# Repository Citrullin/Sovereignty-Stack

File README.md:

# Sovereignty Stack: Federated, Post-ICANN Sovereignty

### A Verifiable, Full-Stack Architecture Bridging Physical Hardware & Cryptographic Manifolds

---

## 1. The Vision

The classical centralized internet and monolithic public blockchain paradigms have reached their limits. Monolithic architectures, burdened by global consensus constraints, speculative volatility, and governance cartels, fail to scale for localized, real-world coordination.

The **Sovereign Stack** bypasses these legacy constraints. Instead of anchoring to central public chains, it coordinates independent, localized **Sector Manifolds** in an autonomous **Sovereign Mesh**. These manifolds peer directly with one another, routing assets and state changes peer-to-peer using **Althea BGP routing** and **cross-manifold Lock mechanisms**, verified via hardware attestation and decentralized proofs.

```mermaid
graph TD
    subgraph Client Layer [Edge Client & Authentication]
        User["NFC Disc / Passkey (3FSA)"] -->|Offline NFC Tap| Node["Local Manifold Node"]
        User -->|SIWE-OIDC Bridge| Koral["Koral Hub: Nextcloud, Gitea, ERPNext"]
    end

    subgraph Execution Layer [Sector Manifolds]
        Node -->|FCFS Tx Pool| Reth["sovereign-reth Stateless Engine"]
        Reth -->|Stateless WitnessDB| WASM["PGlite WASM Edge Sync"]
        Reth -->|6LoWPAN / UDP Mesh| Mesh["Embedded Mesh Network (Avalanche Snow)"]
    end

    subgraph Coordination Layer [Sovereign Mesh & Auditing]
        Reth -->|CMIP / BGP Route| BGP["Althea Pay-per-Forward BGP Routing"]
        BGP -->|Cross-Manifold Locks| Settlement["P2P Settlement & Namespace Enforcement"]
        Audit["DAO Verifiable Auditing"] -->|DAS & Witness Proofs| IPFS["IPFS Storage"]
    end

    style Node fill:#1e222a,stroke:#528bff,stroke-width:1.5px,color:#abb2bf
    style Reth fill:#1e222a,stroke:#528bff,stroke-width:1.5px,color:#abb2bf
    style BGP fill:#1e222a,stroke:#98c379,stroke-width:1.5px,color:#abb2bf
    style Koral fill:#1e222a,stroke:#c678dd,stroke-width:1px,color:#abb2bf
```

This is a pragmatic, local-first approach to decentralization: bringing real-world systems, self-hosted services, and physical industrial hardware together and enforcing coordination via verifiable cryptography.

---

## 2. Key Architecture Components

- **Physicalization of Trust (L0 Hardware):** Trust is anchored directly in physical hardware. `sovereign-reth` runs on bare-metal physical nodes and smart [bit.block microbricks](hardware/bit.block/), using physical [NFC Social Badges](hardware/tiny-pay/) for 3-Factor Sovereign Auth and Crypto-Native Cash (using post-quantum W-OTS+).
- **Post-ICANN BGP Routing & Namespace Enforcement:** Manifolds function as Autonomous Systems (AS), completely replacing legacy IP/DNS. Cross-manifold transactions are routed like IP packets using Althea pay-per-forward economics and dynamic BGP negotiations with complete namespace enforcement.
- **Stateless Execution (`sovereign-reth` & Blind Courier):** Nodes operate statelessly on physical edge hardware, implementing **Blind Courier** for private, stateless witness routing. Embedded WASM CRDT databases (PGlite) handle zero-latency edge synchronization.
- **Universal `did:peer:4` Identity:** Decentralized identities replace IPs and Web2 logins. A single 256-bit entropy seed derives keys for EVM execution (secp256k1), WireGuard peering (Ed25519), and Sync Committees (BLS12-381) via BIP-32.
- **Decentralized Service Level Agreements (DSLA):** Subjective legal contracts are replaced by deterministic hardware **Heartbeat Oracles** and **Actuator Kill-Switches** enforcing pre-emptive compliance.
- **Automated Epistemology Engine:** A machine-verifiable pipeline that binds sociological intent ([Gherkin scenarios](docs/architecture/testing/features/)) to formal mathematical specifications (TLA+) and cryptographically signed execution traces ([OCI/TPM attestations](docs/architecture/verification/51_confidential_deployment_oci_surgery.md)). This forms the absolute truth boundary of the manifold by modeling a **Quantum Superposition** of all possible agent outcomes.

---

## 3. How to Read This Repository

The Sovereign Stack is a theory-driven architecture. The repository is structured to guide you from foundational physics to technical implementation:

1. 📚 **[Quantum Social Physics (QSP) Paper](QUANTUM_SOCIAL_PHYSICS.md):** Start here. This academic paper defines the formal mathematics behind the stack (Velocity Economics, Topological Pathologies, and Resonant Coherence).
2. 📖 **[The Whitebook](whitebook/):** A comprehensive 15-chapter technical specification detailing how the QSP theory is implemented across Identity, Execution, Routing, and Physical Infrastructure.
3. 🧠 **[Concepts Archive](concepts/):** A rich directory of 36 deep-dive philosophical and technical essays expanding on individual mechanics.
4. 💻 **[`sovereign-reth` Execution Engine](crates/):** The Rust implementation of the Sovereign Stack, featuring custom FCFS transaction pools, stateless execution, and cross-manifold BGP intent routing.

---

## 4. Trust & Security Taxonomy

We approach sovereignty not as a collection of apps, but as a formally verifiable ecosystem defined by a strict **Trust Taxonomy**:
- **L0 (Hardware):** Secure Elements and hardware entropy.
- **L1 (Kernel/OS):** Strict deterministic process isolation.
- **L2 (Network):** Metadata obfuscation and privacy routing.
- **L3 (Identity):** Cryptographically defined DIDs and Verifiable Credentials.
- **L4 (User Agency):** UI/UX designed to prevent dark patterns and enforce informed consent.

The stack solves the "Sovereignty Gap" by replacing the "Trust but Verify" paradigm with a **"Verify, then Trust"** architecture. Through Decentralized Verification, Zero-Trust Orchestration, and transparent threat modeling, the stack guarantees that users own not just their data, but the orchestration logic itself.

### Strategic Roadmap: Eliminating Operator Trust

| Component | Legacy Model | Sovereign Recommendation | Why? |
| :--- | :--- | :--- | :--- |
| **Logic** | Helm / Jinja | OCI Layer Patches (`umoci`) | Eliminates template injection/leaks. |
| **Integrity** | Ansible Scripts | `in-toto` Attestations | Cryptographic proof of physical & digital "Why/How". |
| **Isolation** | Standard Podman | Confidential Containers (CoCo) | Host cannot read container memory. |
| **Trust Root** | Admin Password | Keylime + TPM 2.0 | Hardware-level detection of physical tampering. |
| **Build Env** | Shared VM/Runner | TEE (Intel TDX / AMD SEV) | Build process is a "Black Box" even to root. |

For the formal threat model, see [`docs/architecture/THREAT_MODEL.md`](docs/architecture/THREAT_MODEL.md).
For the tunneling protocol and intent-based routing, see the [Unified Manifold Interface (UMI)](docs/architecture/UNIFIED_MANIFOLD_INTERFACE.md).

---

## 5. Repository Directory Index

The repository contains both hardware specifications and software execution engines:

| Directory | Sub-components & Function | Key Concept Chapters |
|---|---|---|
| [`whitebook/`](whitebook/) | Comprehensive 15-chapter technical specifications. | §01–§15 |
| [`concepts/`](concepts/) | Concept manifesto, $TINY tokenomics, and proof-of-work anchors. | §00–§54 |
| [`hardware/bit.block/`](hardware/bit.block/) | Smart microbrick PCB (KiCAD), 3D prints, and WebGL emulator. | §12, §13, §11 |
| [`hardware/gachapon/`](hardware/gachapon/) | Gachapon machine design — Physicalized Based Rollup Node. | §03, §15, §22 |
| [`hardware/tiny-pay/`](hardware/tiny-pay/) | NFC Tiny Disc (Social Badge + Wahfare branded disc). | §22, §18, §43 |
| [`hardware/tinyblock/`](hardware/tinyblock/) | LDraw set designs (Astronaut, Lighthouse). | §44 |
| [`software/bit.block/`](software/bit.block/) | Arduino WoT firmware — W3C Thing Description PoC. | §12, §16, §11 |
| [`software/tinyblock/`](software/tinyblock/) | LDraw parts submodule + AI training benchmark images. | §44 |
| [`software/web-of-things/`](software/web-of-things/) | RIOT-OS WoT + Arduino WebThings submodules. | §12, §13 |
| [`software/koral/`](software/koral/) | Sovereign Hub — k8s, Nextcloud, ERPNext, OIDC, Istio. | §04, §16, §18, §46 |
| [`software/chain/`](software/chain/) | Smart contract specs: $TINY, ERC-3475, deIBAN. | §39–§43, §46 |

---

## 6. Quick Start

Clone the repository and initialize all hardware/software submodules:

```bash
# Clone with submodules
git clone --recurse-submodules https://github.com/citrullin/sovereign_stack_vision.git

# Or if already cloned, initialize submodules:
git submodule update --init
```

### Submodules Included:
- `software/tinyblock/microblock_ldraw`: LDraw parts library for physical microblocks.
- `software/web-of-things/RIOT-OS`: W3C WoT CoAP module for IoT RIOT-OS.
- `software/web-of-things/arduino`: WebThings fork (WoT TD 1.0) for Arduino/ESP32.

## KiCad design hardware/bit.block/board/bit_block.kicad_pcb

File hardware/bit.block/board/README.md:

# PCB Files for the Astronaut on Moon Base Set

The offline local-only voice recognition tinyblock set. Full KiCAD files in this directory.

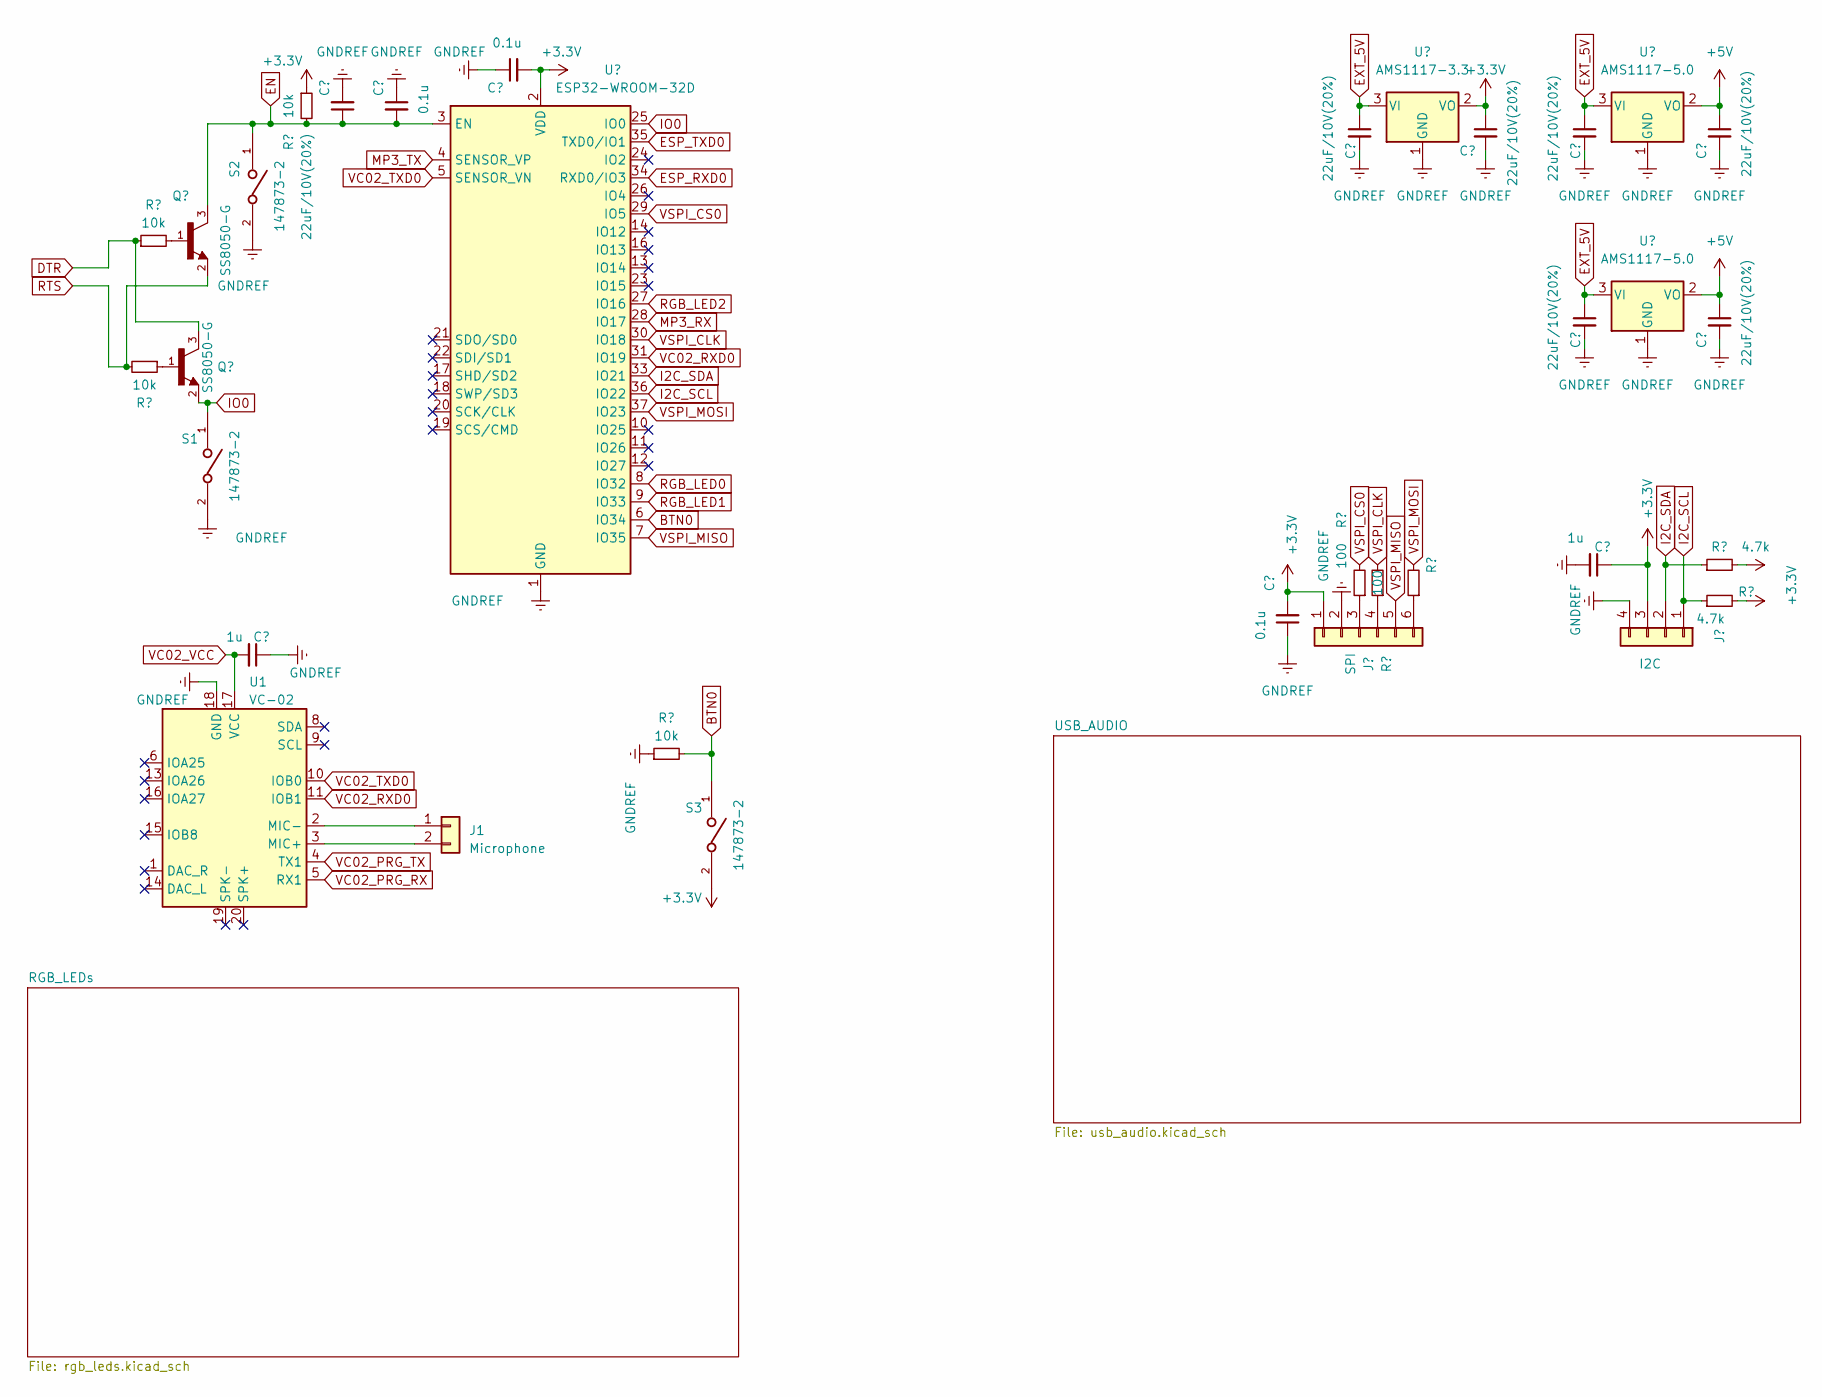
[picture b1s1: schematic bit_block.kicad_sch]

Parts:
C1, C10: 1u; C_0402_1005Metric
C2, C6, C7, C8, C9, C11, C12: 22uF/10V(20%); CP_EIA-3216-18_Kemet-A
C3, C4, C5: 0.1u; C_0402_1005Metric
J1: Microphone; PinHeader_1x02_P2.00mm_Vertical
J2: SPI; JST_SH_SM06B-SRSS-TB_1x06-1MP_P1.00mm_Horizontal
J3: I2C; JST_SH_SM04B-SRSS-TB_1x04-1MP_P1.00mm_Horizontal
Q1, Q2: SS8050-G; TRANS_SS8050-G; PARTREV A
R1, R2, R3, R4: 10k; R_0402_1005Metric
R5, R6, R7: 100; R_0402_1005Metric
R8, R9: 4.7k; R_0402_1005Metric
S1, S2, S3: 147873-2; SW_147873-2; PARTREV K3
U1: VC-02; Ai-Thinker-VC02
U2: ESP32-WROOM-32D; ESP32-WROOM-32
U3: AMS1117-3.3; SOT-223-3_TabPin2
U4, U5: AMS1117-5.0; SOT-223-3_TabPin2

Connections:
+3.3V: C4.2, C5.2, C7.1, C10.1, J2.1, J3.3, R3.1, R8.2, R9.2, S3.2, U2.2 (VDD), U3.2 (VO); also elsewhere on the board
+5V: C11.1, C12.1, U4.2 (VO), U5.2 (VO); also elsewhere on the board
BTN0: R4.2, S3.1, U2.6 (IO34)
DTR: Q1.3, R2.1; also elsewhere on the board
EN: C2.1, C3.2, Q2.3, R3.2, S2.1, U2.3 (EN)
ESP_RXD0: U2.34 (RXD0/IO3); also elsewhere on the board
ESP_TXD0: U2.35 (TXD0/IO1); also elsewhere on the board
EXT_5V: C6.1, C8.1, C9.1, U3.3 (VI), U4.3 (VI), U5.3 (VI); also elsewhere on the board
GNDREF: C1.1, C2.2, C3.1, C4.1, C5.1, C6.2, C7.2, C8.2, C9.2, C10.2, C11.2, C12.2, J2.2, J3.4, R4.1, S1.2, S2.2, U1.18 (GND), U2.1 (GND), U2.15 (GND), U2.38 (GND), U2.39 (GND), U3.1 (GND), U4.1 (GND), U5.1 (GND); also elsewhere on the board
I2C_SCL: J3.1, R9.1, U2.36 (IO22)
I2C_SDA: J3.2, R8.1, U2.33 (IO21)
IO0: Q1.2, S1.1, U2.25 (IO0)
MP3_RX: U2.28 (IO17); also elsewhere on the board
MP3_TX: U2.4 (SENSOR_VP); also elsewhere on the board
unnamed: J1.1, U1.2 (MIC-)
unnamed: J1.2, U1.3 (MIC+)
unnamed: J2.3, R5.1
unnamed: J2.4, R6.1
unnamed: J2.6, R7.1
unnamed: Q1.1, R1.1
unnamed: Q2.1, R2.2
RGB_LED0: U2.8 (IO32); also elsewhere on the board
RGB_LED1: U2.9 (IO33); also elsewhere on the board
RGB_LED2: U2.27 (IO16); also elsewhere on the board
RTS: Q2.2, R1.2; also elsewhere on the board
VC02_PRG_RX: U1.5 (RX1); also elsewhere on the board
VC02_PRG_TX: U1.4 (TX1); also elsewhere on the board
VC02_RXD0: U1.11 (IOB1), U2.31 (IO19)
VC02_TXD0: U1.10 (IOB0), U2.5 (SENSOR_VN)
VC02_VCC: C1.2, U1.17 (VCC); also elsewhere on the board
VSPI_CLK: R6.2, U2.30 (IO18)
VSPI_CS0: R5.2, U2.29 (IO5)
VSPI_MISO: J2.5, U2.7 (IO35)
VSPI_MOSI: R7.2, U2.37 (IO23)

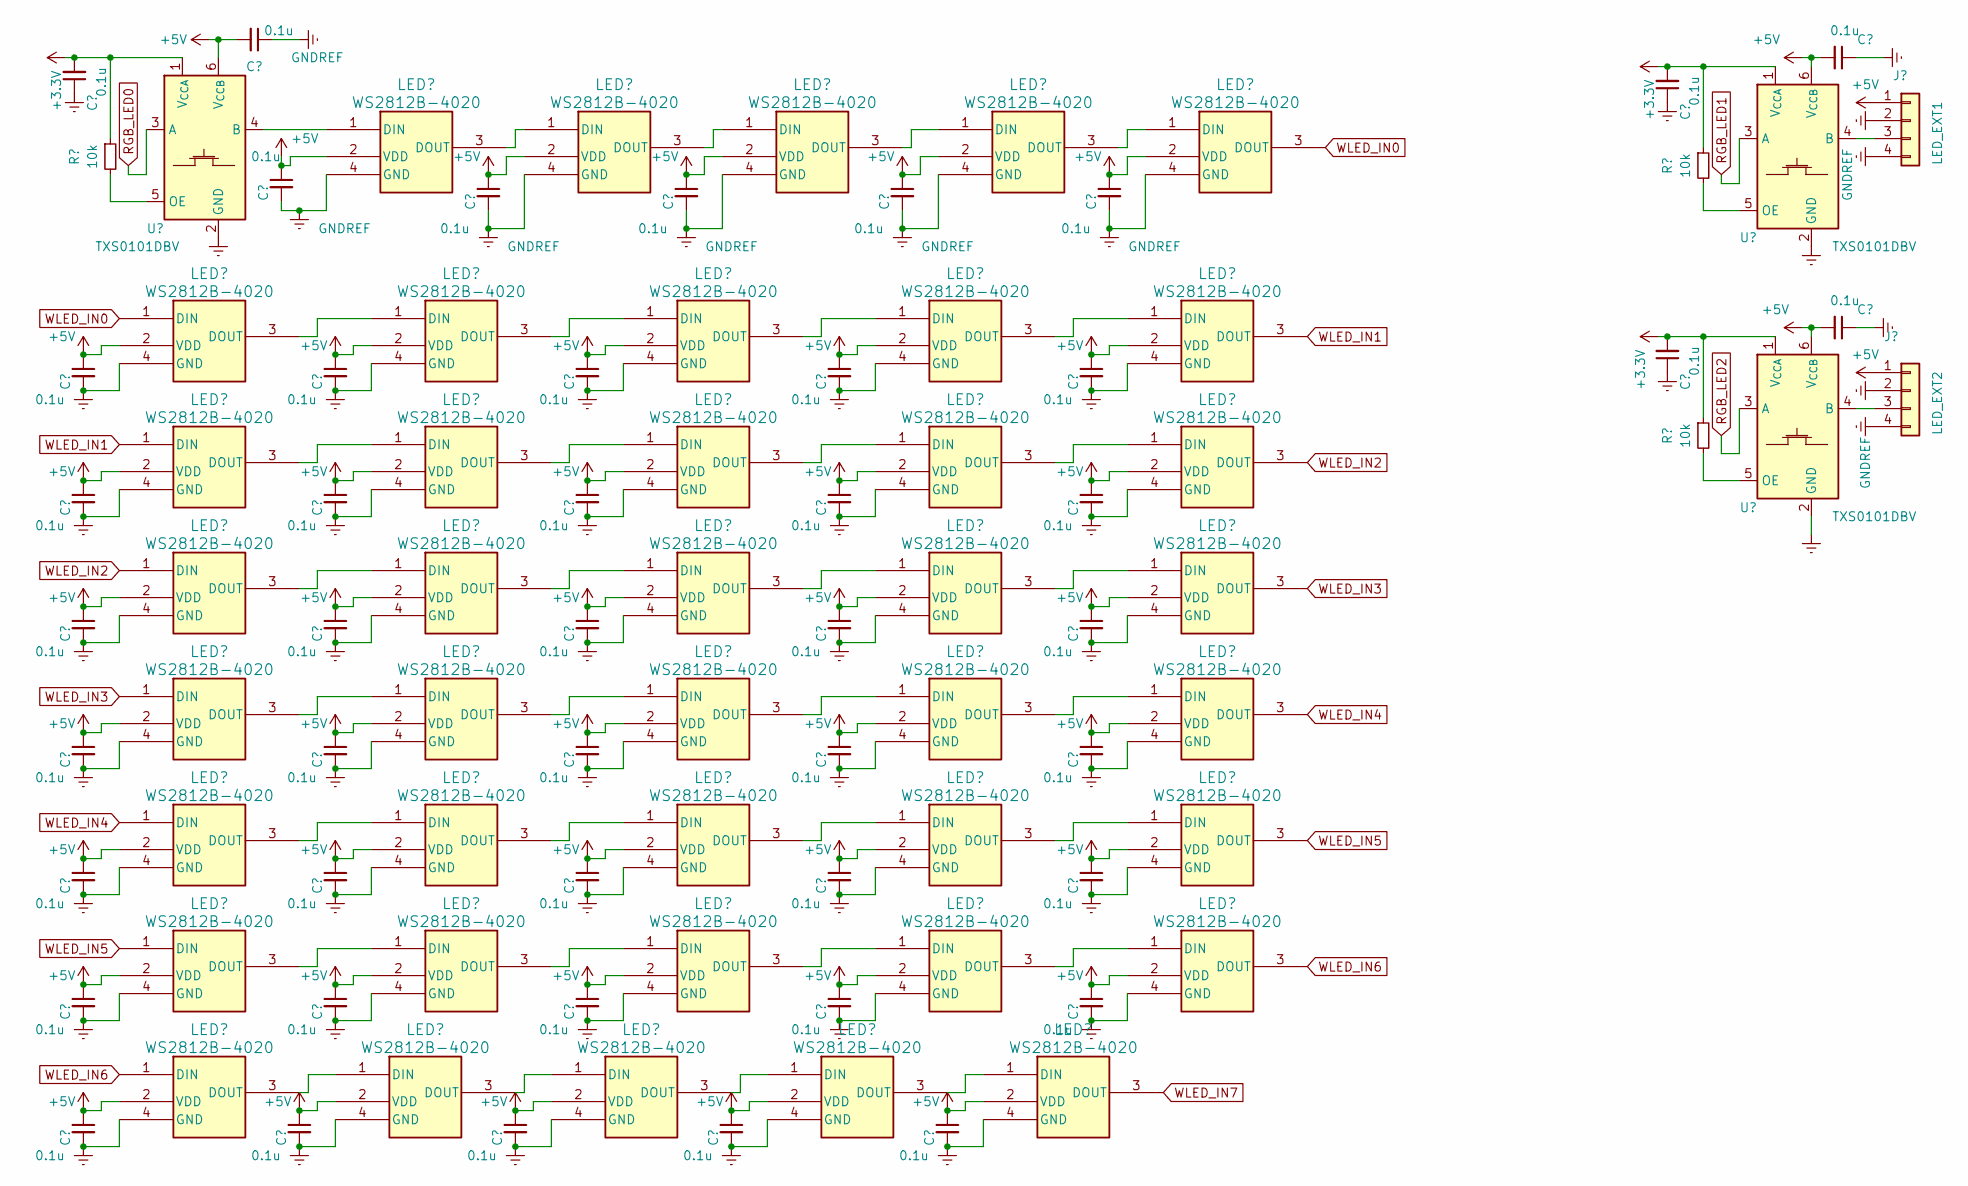
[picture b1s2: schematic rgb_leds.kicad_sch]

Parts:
C13, C14, C15, C16, C17, C18, C19, C20, C21, C22, C23, C24, C25, C26, C27, C28, C29, C30, C31, C32, C33, C34, C35, C36, C37, C38, C39, C40, C41, C42, C43, C44, C45, C46, C47, C48, C49, C50, C51, C52, C53, C54, C55, C56, C57, C58: 0.1u; C_0402_1005Metric
J4: LED_EXT1; JST_SH_SM04B-SRSS-TB_1x04-1MP_P1.00mm_Horizontal
J5: LED_EXT2; JST_SH_SM04B-SRSS-TB_1x04-1MP_P1.00mm_Horizontal
LED1, LED2, LED3, LED4, LED5, LED6, LED7, LED8, LED9, LED10, LED11, LED12, LED13, LED14, LED15, LED16, LED17, LED18, LED19, LED20, LED21, LED22, LED23, LED24, LED25, LED26, LED27, LED28, LED29, LED30, LED31, LED32, LED33, LED34, LED35, LED36, LED37, LED38, LED39, LED40: WS2812B-4020; SMD_WS2812B-4020
R10, R11, R12: 10k; R_0402_1005Metric
U6, U7, U8: TXS0101DBV; SOT-23-6

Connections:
+3.3V: C13.2, C55.2, C56.2, R10.1, R11.1, R12.1, U6.1 (V_{CCA}), U7.1 (V_{CCA}), U8.1 (V_{CCA}); also elsewhere on the board
+5V: C14.1, C15.1, C16.1, C17.1, C18.1, C19.1, C20.1, C21.2, C22.1, C23.1, C24.1, C25.1, C26.1, C27.1, C28.1, C29.1, C30.1, C31.1, C32.1, C33.1, C34.1, C35.1, C36.1, C37.1, C38.1, C39.1, C40.1, C41.1, C42.1, C43.1, C44.1, C45.1, C46.1, C47.1, C48.1, C49.1, C50.1, C51.1, C52.1, C53.1, C54.1, C57.2, C58.2, J4.1, J5.1, LED1.2 (VDD), LED2.2 (VDD), LED3.2 (VDD), LED4.2 (VDD), LED5.2 (VDD), LED6.2 (VDD), LED7.2 (VDD), LED8.2 (VDD), LED9.2 (VDD), LED10.2 (VDD), LED11.2 (VDD), LED12.2 (VDD), LED13.2 (VDD), LED14.2 (VDD), LED15.2 (VDD), LED16.2 (VDD), LED17.2 (VDD), LED18.2 (VDD), LED19.2 (VDD), LED20.2 (VDD), LED21.2 (VDD), LED22.2 (VDD), LED23.2 (VDD), LED24.2 (VDD), LED25.2 (VDD), LED26.2 (VDD), LED27.2 (VDD), LED28.2 (VDD), LED29.2 (VDD), LED30.2 (VDD), LED31.2 (VDD), LED32.2 (VDD), LED33.2 (VDD), LED34.2 (VDD), LED35.2 (VDD), LED36.2 (VDD), LED37.2 (VDD), LED38.2 (VDD), LED39.2 (VDD), LED40.2 (VDD), U6.6 (V_{CCB}), U7.6 (V_{CCB}), U8.6 (V_{CCB}); also elsewhere on the board
GNDREF: C13.1, C14.2, C15.2, C16.2, C17.2, C18.2, C19.2, C20.2, C21.1, C22.2, C23.2, C24.2, C25.2, C26.2, C27.2, C28.2, C29.2, C30.2, C31.2, C32.2, C33.2, C34.2, C35.2, C36.2, C37.2, C38.2, C39.2, C40.2, C41.2, C42.2, C43.2, C44.2, C45.2, C46.2, C47.2, C48.2, C49.2, C50.2, C51.2, C52.2, C53.2, C54.2, C55.1, C56.1, C57.1, C58.1, J4.2, J4.4, J5.2, J5.4, LED1.4 (GND), LED2.4 (GND), LED3.4 (GND), LED4.4 (GND), LED5.4 (GND), LED6.4 (GND), LED7.4 (GND), LED8.4 (GND), LED9.4 (GND), LED10.4 (GND), LED11.4 (GND), LED12.4 (GND), LED13.4 (GND), LED14.4 (GND), LED15.4 (GND), LED16.4 (GND), LED17.4 (GND), LED18.4 (GND), LED19.4 (GND), LED20.4 (GND), LED21.4 (GND), LED22.4 (GND), LED23.4 (GND), LED24.4 (GND), LED25.4 (GND), LED26.4 (GND), LED27.4 (GND), LED28.4 (GND), LED29.4 (GND), LED30.4 (GND), LED31.4 (GND), LED32.4 (GND), LED33.4 (GND), LED34.4 (GND), LED35.4 (GND), LED36.4 (GND), LED37.4 (GND), LED38.4 (GND), LED39.4 (GND), LED40.4 (GND), U6.2 (GND), U7.2 (GND), U8.2 (GND); also elsewhere on the board
unnamed: J4.3, U7.4 (B)
unnamed: J5.3, U8.4 (B)
unnamed: LED1.3 (DOUT), LED10.1 (DIN)
unnamed: LED7.3 (DOUT), LED9.1 (DIN)
unnamed: LED8.1 (DIN), U6.4 (B)
unnamed: LED10.3 (DOUT), LED18.1 (DIN)
unnamed: LED2.3 (DOUT), LED11.1 (DIN)
unnamed: LED11.3 (DOUT), LED19.1 (DIN)
unnamed: LED3.3 (DOUT), LED12.1 (DIN)
unnamed: LED12.3 (DOUT), LED20.1 (DIN)
unnamed: LED4.3 (DOUT), LED13.1 (DIN)
unnamed: LED13.3 (DOUT), LED21.1 (DIN)
unnamed: LED5.3 (DOUT), LED14.1 (DIN)
unnamed: LED14.3 (DOUT), LED22.1 (DIN)
unnamed: LED6.3 (DOUT), LED15.1 (DIN)
unnamed: LED15.3 (DOUT), LED23.1 (DIN)
unnamed: LED8.3 (DOUT), LED16.1 (DIN)
unnamed: LED16.3 (DOUT), LED24.1 (DIN)
unnamed: LED9.3 (DOUT), LED17.1 (DIN)
unnamed: LED17.3 (DOUT), LED25.1 (DIN)
unnamed: LED18.3 (DOUT), LED26.1 (DIN)
unnamed: LED19.3 (DOUT), LED27.1 (DIN)
unnamed: LED20.3 (DOUT), LED28.1 (DIN)
unnamed: LED21.3 (DOUT), LED29.1 (DIN)
unnamed: LED22.3 (DOUT), LED30.1 (DIN)
unnamed: LED23.3 (DOUT), LED31.1 (DIN)
unnamed: LED24.3 (DOUT), LED32.1 (DIN)
unnamed: LED25.3 (DOUT), LED33.1 (DIN)
unnamed: LED26.3 (DOUT), LED34.1 (DIN)
unnamed: LED27.3 (DOUT), LED35.1 (DIN)
unnamed: LED28.3 (DOUT), LED36.1 (DIN)
unnamed: LED29.3 (DOUT), LED37.1 (DIN)
unnamed: LED30.3 (DOUT), LED38.1 (DIN)
unnamed: LED31.3 (DOUT), LED39.1 (DIN)
unnamed: LED32.3 (DOUT), LED40.1 (DIN)
unnamed: R10.2, U6.5 (OE)
unnamed: R11.2, U7.5 (OE)
unnamed: R12.2, U8.5 (OE)
RGB_LED0: U6.3 (A); also elsewhere on the board
RGB_LED1: U7.3 (A); also elsewhere on the board
RGB_LED2: U8.3 (A); also elsewhere on the board
WLED_IN0: LED1.1 (DIN), LED40.3 (DOUT)
WLED_IN1: LED2.1 (DIN), LED34.3 (DOUT)
WLED_IN2: LED3.1 (DIN), LED35.3 (DOUT)
WLED_IN3: LED4.1 (DIN), LED36.3 (DOUT)
WLED_IN4: LED5.1 (DIN), LED37.3 (DOUT)
WLED_IN5: LED6.1 (DIN), LED38.3 (DOUT)
WLED_IN6: LED7.1 (DIN), LED39.3 (DOUT)
WLED_IN7: LED33.3 (DOUT)

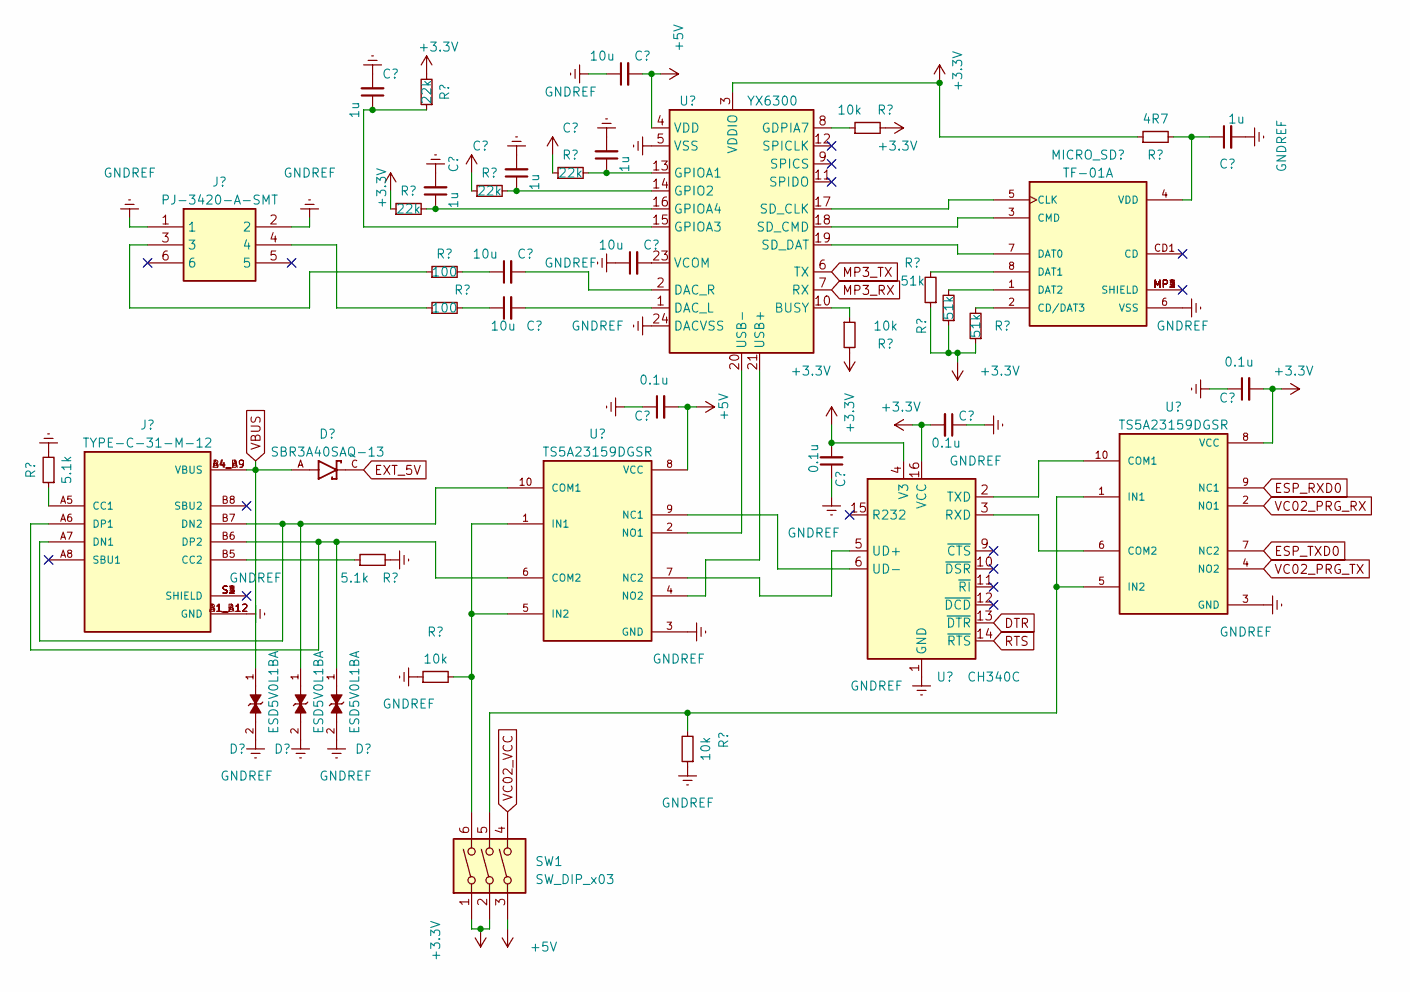
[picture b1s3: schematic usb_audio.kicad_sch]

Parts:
C59, C60, C63, C64, C70: 1u; C_0402_1005Metric
C61, C62, C65, C66: 10u; C_0402_1005Metric
C67, C68, C69, C71: 0.1u; C_0402_1005Metric
D1, D2, D4: ESD5V0L1BA; D_SOD-323
D3: SBR3A40SAQ-13; DIOM5226X230N; PARTREV 9-2
J6: PJ-3420-A-SMT; PJ3420ASMT; Manufacturer_Part_Number PJ-3420-A-SMT
J7: TYPE-C-31-M-12; HRO_TYPE-C-31-M-12; PARTREV 2020.12.08
MICRO_SD1: TF-01A
R13, R14: 5.1k; R_0402_1005Metric
R15, R16, R20, R21: 22k; R_0402_1005Metric
R17, R22, R23, R24: 10k; R_0402_1005Metric
R18, R19: 100; R_0402_1005Metric
R25, R26, R27: 51k; R_0402_1005Metric
R28: 4R7; R_0402_1005Metric
SW1: SW_DIP_x03; SW_DS05-127-2-03BK-SMT-TR
U9, U12: TS5A23159DGSR; MSOP-10_3x3mm_P0.5mm; PARTREV H
U10: YX6300; SSOP-24_3.9x8.7mm_P0.635mm
U11: CH340C; SOIC-16_3.9x9.9mm_P1.27mm

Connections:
+3.3V: C68.2, C69.2, C71.2, R15.1, R16.2, R20.1, R21.1, R23.2, R24.2, R25.1, R26.1, R27.1, R28.1, SW1.1, SW1.2, U10.3 (VDDIO), U11.4 (V3), U11.16 (VCC), U12.8 (VCC); also elsewhere on the board
+5V: C65.2, C67.2, SW1.3, U9.8 (VCC), U10.4 (VDD); also elsewhere on the board
DTR: U11.13 (~DTR); also elsewhere on the board
ESP_RXD0: U12.9 (NC1); also elsewhere on the board
ESP_TXD0: U12.7 (NC2); also elsewhere on the board
EXT_5V: D3.C; also elsewhere on the board
GNDREF: C59.2, C60.2, C63.2, C64.2, C65.1, C66.1, C67.1, C68.1, C69.1, C70.2, C71.1, D1.2, D2.2, D4.2, J6.1, J6.2, J7.A1_B12 (GND), J7.B1_A12 (GND), MICRO_SD1.6 (VSS), R13.2, R14.2, R17.1, R22.1, U9.3 (GND), U10.5 (VSS), U10.24 (DACVSS), U11.1 (GND), U12.3 (GND); also elsewhere on the board
MP3_RX: U10.7 (RX); also elsewhere on the board
MP3_TX: U10.6 (TX); also elsewhere on the board
unnamed: C61.1, R18.2
unnamed: C62.1, R19.2
unnamed: J6.3, R18.1
unnamed: J6.4, R19.1
unnamed: J7.A5 (CC1), R13.1
unnamed: J7.B5 (CC2), R14.1
unnamed: D2.1, J7.A7 (DN1), J7.B7 (DN2), U9.10 (COM1)
unnamed: D4.1, J7.A6 (DP1), J7.B6 (DP2), U9.6 (COM2)
unnamed: MICRO_SD1.2 (CD/DAT3), R27.2
unnamed: MICRO_SD1.5 (CLK), U10.17 (SD_CLK)
unnamed: MICRO_SD1.3 (CMD), U10.18 (SD_CMD)
unnamed: MICRO_SD1.7 (DAT0), U10.19 (SD_DAT)
unnamed: MICRO_SD1.8 (DAT1), R25.2
unnamed: MICRO_SD1.1 (DAT2), R26.2
unnamed: C70.1, MICRO_SD1.4 (VDD), R28.2
unnamed: R17.2, SW1.6, U9.1 (IN1), U9.5 (IN2)
unnamed: R23.1, U10.10 (BUSY)
unnamed: C62.2, U10.1 (DAC_L)
unnamed: C61.2, U10.2 (DAC_R)
unnamed: R24.1, U10.8 (GDPIA7)
unnamed: C63.1, R20.2, U10.14 (GPIO2)
unnamed: C64.1, R21.2, U10.13 (GPIOA1)
unnamed: C59.1, R16.1, U10.15 (GPIOA3)
unnamed: C60.1, R15.2, U10.16 (GPIOA4)
unnamed: U9.4 (NO2), U10.21 (USB+)
unnamed: U9.2 (NO1), U10.20 (USB-)
unnamed: C66.2, U10.23 (VCOM)
unnamed: U11.3 (RXD), U12.6 (COM2)
unnamed: U11.2 (TXD), U12.10 (COM1)
unnamed: U9.7 (NC2), U11.5 (UD+)
unnamed: U9.9 (NC1), U11.6 (UD-)
unnamed: R22.2, SW1.5, U12.1 (IN1), U12.5 (IN2)
RTS: U11.14 (~RTS); also elsewhere on the board
VBUS: D1.1, D3.A, J7.A4_B9 (VBUS), J7.B4_A9 (VBUS)
VC02_PRG_RX: U12.2 (NO1); also elsewhere on the board
VC02_PRG_TX: U12.4 (NO2); also elsewhere on the board
VC02_VCC: SW1.4; also elsewhere on the board

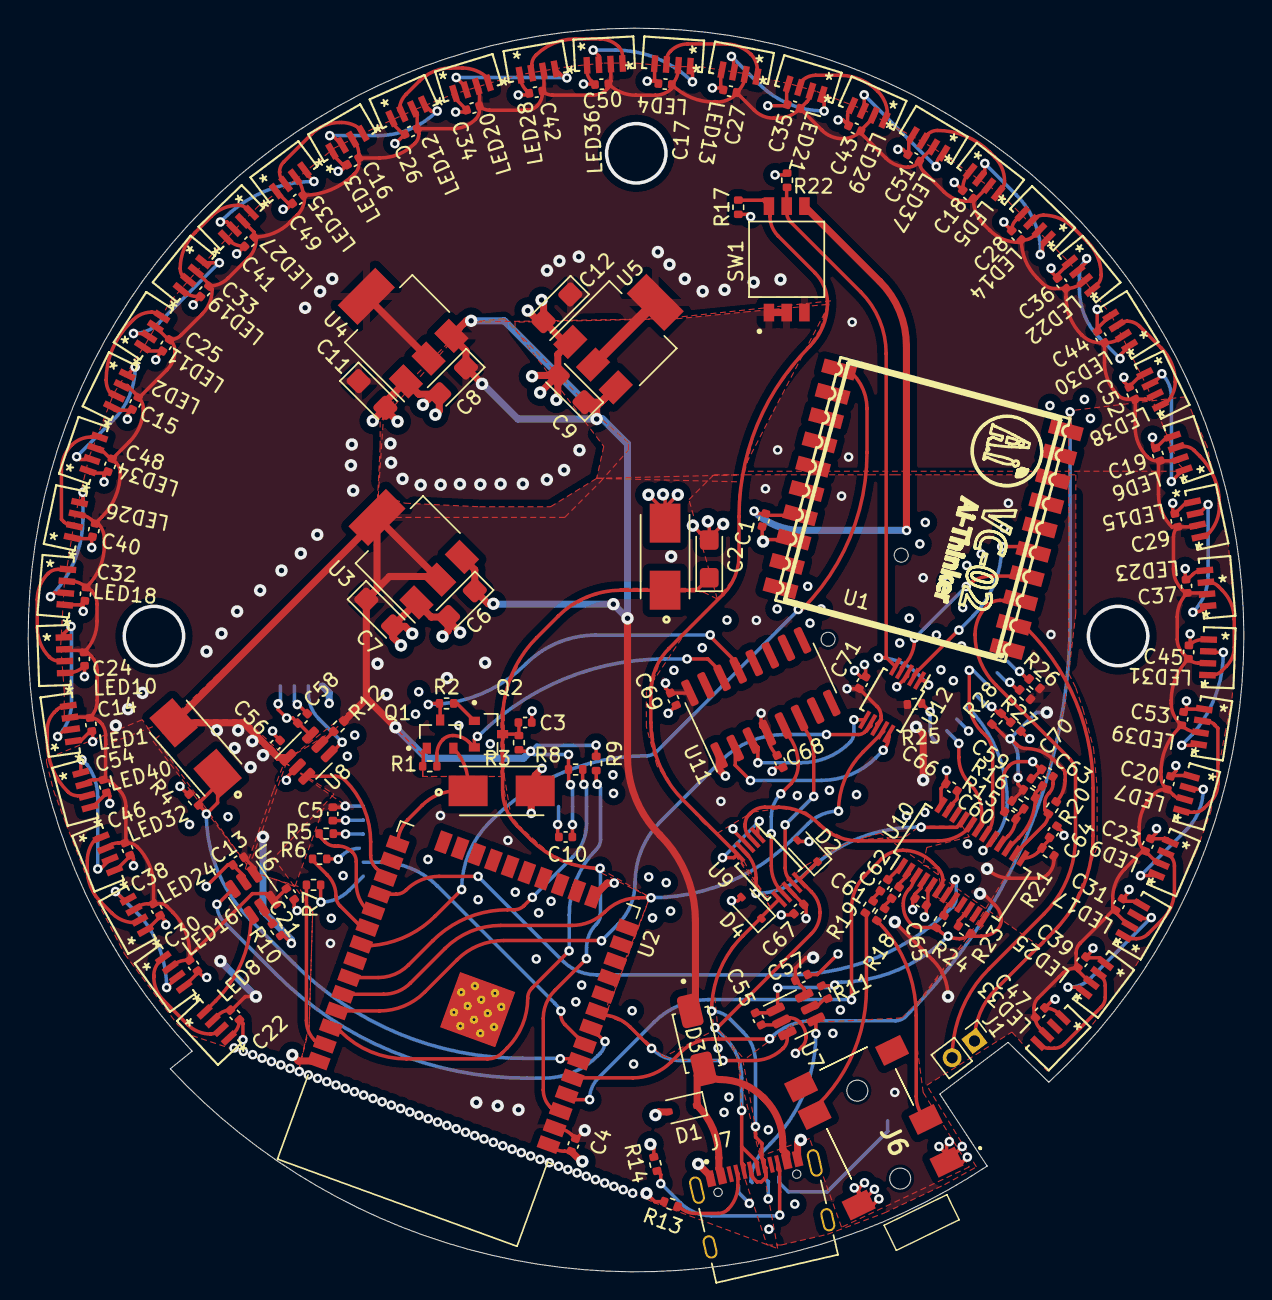
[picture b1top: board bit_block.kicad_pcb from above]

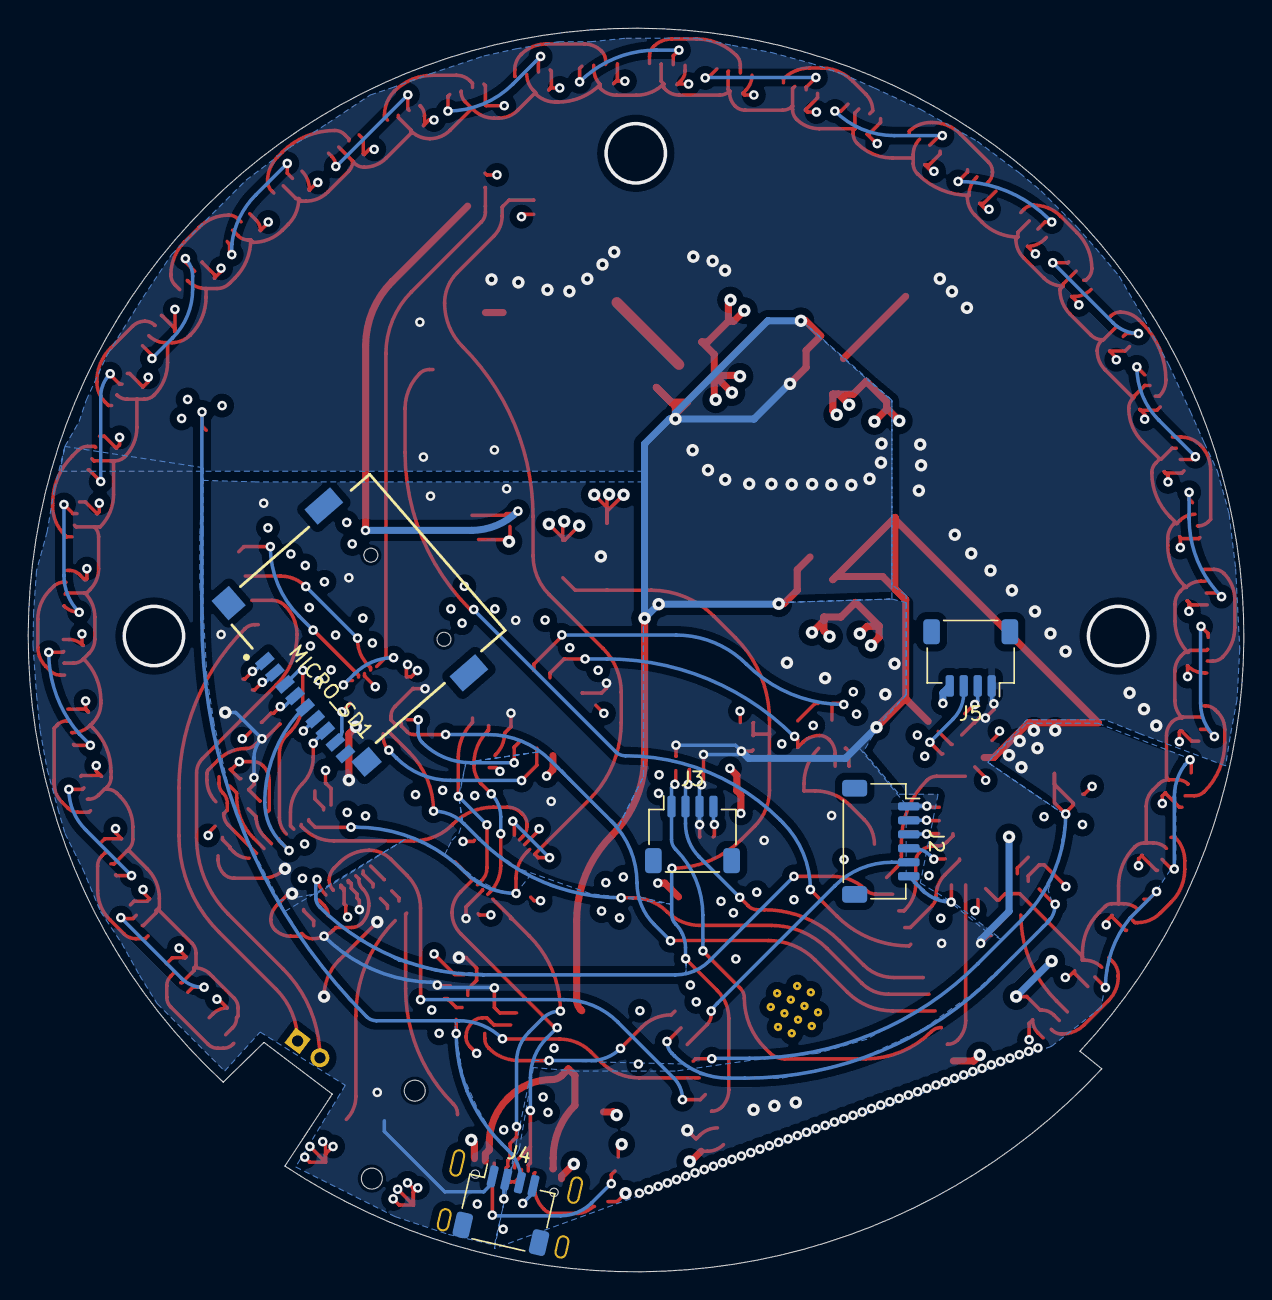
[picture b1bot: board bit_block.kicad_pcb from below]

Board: 4 copper layers, 87.0 x 89.0 mm, 169 parts (5 on the bottom side), 112 nets.

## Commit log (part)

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2026-04-19 v0.1
2026-05-10 First monorepo setup + some submodules structure + Content
2026-05-11 Add more videos and pictures, pdf references manual
2026-05-11 Add videos to readme file and add additional pictures and videos
2026-05-11 Add README with investment thesis and some details
2026-05-11 Add more comprehensive README.md to software
2026-05-11 Fixup: Instructions and add another instruction test case
2026-05-11 Improve several READMEs
2026-05-12 Add Bit.block Arduino WoT example for offline speech recognition and music playing (safecon demo)
2026-05-12 First deeper structural cleanup and refactoring.
2026-05-13 feat(manifesto): Add Sociological Discovery layer and W3C critique
    - Added §0: The W3C Failure, addressing the Founder Myth, historical erasure, and the WoT DAO vision.
    - Added Part XII: Sociological Discovery & Thermodynamics (§47-49).
    - §47: Thermodynamics of Trust, defining Digital Families as local low-entropy clusters and detailing pluralistic value discovery and collective investment.
    - §48: Fluid Privacy, introducing Merkle-proven DMs and cross-pod agent syncing via IPFS.
    - §49: Digital Third Place, establishing high school social dynamics, ActivityPub integration, and the gamification of discovery via physical NFT NFC badges.
    - Updated root README to feature a concise, pragmatic
2026-05-13 feat(manifesto): Add Decentralized Verification layer and DAO Accountability
    - Added §50: The Final Boss of DevOps (Decentralized Verification), defining OCI-on-IPFS and ZK-Attestations.
    - Implemented DAO Certification workflow and AI Auditor deep-dive matching for local config verification.
    - Added §48.4: Individual Sovereignty vs. DAO Accountability, separating meta-data from content to empower whistleblowers and solve lobbying accountability.
    - Updated WoT README to extend Thing Descriptions with DIDs and OCI hashes for Public Verification.
    - Updated Koral Hub and Chain READMEs to integrate Kyverno policies and the WoT DAO Certification Anchor.
    - Updated indices to reflect 51-section re
2026-05-13 feat(auditor): Rough implementation of the end to end sociological blockchain framework
    - Formalized Section 53: Agentic Protocol Auditor in the concept manifesto.
    - Added FIXME in root README regarding index refactoring.
    - Scaffolded MCP Server to allow AI Agents to interact with Yocto manifests and OCI registries.
    - Scaffolded meta-sovereignty Yocto layer to compile Rust embedded binaries.
    - Translated all 54 manifesto concepts into Gherkin BDD verification suites:
    - philosophical_thermodynamics.feature
2026-05-13 docs: Add navigation READMEs, math templates, and tooling config
    - 24 missing README.md files generated and committed across all directories.
    - Concept subdirectory READMEs cross-reference manifesto sections by number.
    - docs/ and software/ READMEs describe the A2A/verification pipeline flow.
    - Extracted inline math models from one-shot scripts into templates/:
    - formal_math_elastic_supply.md (§7.5 Security-Velocity Equation)
    - formal_math_tiny_tokenomics.md (Margin Call Logic)
2026-05-13 feat(compliance): Implement Automated Compliance Evidence Gherkin scenarios
    - Added compliance_automation.feature with ISO 9001, 27001, 42001, 31000, and 45001 scenarios.
    - Integrated European Sovereign Stack (ES³) data sovereignty (PII isolation) requirements.
    - Established 'AuditBot' evidence collection loop for ERPNext/SIWE integration.
    - Updated docs/architecture/testing/features/README.md with the new suite index.
2026-05-13 feat(telemetry): Formalize A2A telemetry with hash-chained logs and secure podman traces
    This commit introduces:
    - A non-repudiable audit log system (verification_history.jsonl).
    - Secure, containerized shell session recording (podman_trace.sh).
    - Hardened cosign signing pipeline with restricted volume mounts.
    - Merit-based governance banding and automated temporal merit decay.
    - Supply Chain Soundness (SCS) scoring for build verification.
2026-05-13 feat(koral): Initialize Koral and add k3s-hub submodule
    Pinned to ee44cb1f4aa9964633b780ab1c50254aaa482ec1 for verifiable patch foundation.
2026-05-13 feat(koral): Implement Koral core logic and hardware emulation suite
    This commit introduces:
    - Merit-gated patch verification (verify_patch.py) integrated with A2A governance.
    - Hardware emulation runners for QEMU (VM) and Kata (VT-x isolation).
    - Verifiable OCI artifact signing pipeline (koral_build.py).
    - BDD/TDD hardware emulation test suite.
2026-05-14 docs(qsp): draft conceptual foundation and TDD metrics for Quantum Social Physics
    - Drafts core philosophy for 'Superconductor Archetype' and 'Quantum Shield'
    - Introduces thermodynamic audit framework (THERMODYNAMIC_COHERENCE.md)
    - Aligns A2A telemetry with QSP physics (resonance_velocity, ego_friction) via TDD
    - Transitions governance bands to coherence states (superconducting, coherent, decohering, collapsed)
    - Commits initial Koral governance stubs and verifiable patch tooling currently in progress
2026-05-27 docs: Paradigm shift from Newtonian chains to Quantum Social Physics
    Introduces the foundational QSP mechanics, Quantum Tunneling, Transient State
    Packets, and Thermodynamic State Prediction. This establishes the theoretical
    basis for transitioning from sequential, single-state Blockchains towards
    Multi-Frequency Federated Manifolds.
2026-05-27 feat(hardware): Integrate Triple Mode POS and Passive NFC constraints
    - Resolves logical gaps in POS hardware realities.
    - Establishes Triple Mode architecture (EMV, Passive NFC, Active Java Card).
    - Introduces BLE pairing, in-app relaying, and seed rotation for NFC security.
    - Refines ERC-4337 temporal constraints to a Chained Settlement 5-minute window,
    outlining future migration to FPGA/ASIC sub-second TOTP pulse validation.
2026-05-27 refactor(philosophy): Pivot from Syndicate critique to Regulated Banking Well
    - Abandons the cypherpunk 'Syndicate' framing in favor of the 'Regulated Banking Well'.
    - Supports bank-led centralization of L1 networks as a necessary low-entropy anchor
    for stabilizing volatile speculation.
    - Fixes broken links across conceptual indices to point to the unified anchor well docs.
2026-05-27 feat(epistemology): Introduce TLA+ superposition modeling and LLM registries
    - Reframes LLM interactions in the Epistemological Pipeline as acting *on behalf*
    of users rather than serving as deterministic verifiers.
    - Simplifies formal verification by bounding the possibility space of non-deterministic
    LLM actions using TLA+ Quantum Superposition modeling.
    - Outlines decentralized Manifold-specific agent registries for cross-manifold discovery
    and Block-Building orchestration.
2026-05-27 feat(epistemology): Migrate and refactor legacy architecture to Quantum Social Science
    - Relocates all legacy unnumbered folders under concepts/ into a structured docs/architecture/ tree, resolving all legacy 'Newtonian' sequential models into Sovereign Manifold scaling designs.
    - Frames L1/L2 networks as specialized Internal Manifold Scaling (e.g., Based Rollups/Taiko model) rather than absolute global architectures.
    - Refactors SIWE-OIDC bridges to explicitly utilize Tinyblock and neutral organization orchestration as the primary authentication gateways.
    - Reframes Heartbeat and Actuator Oracles as continuous thermodynamic observer agents reporting directly to the manifold's internal state
2026-05-27 feat(koral): introduce recursive OCI synthesis model and scaffold recipes
    - Extract regional patches and Jinja2 templates for 19 services from legacy Ansible into isolated OCI recipes.
    - Implement koral_synthesis.sh recursive composition engine for dev/prod builds.
    - Configure local Zot registry target.
    - Note: This is an initial commit of the new approach. It is currently in an UNTESTED, NON-BUILDABLE state, as the legacy Ansible setup is currently broken and this new synthesis approach has not bee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
2026-05-27 docs(koral): open-source notice and document Recursive OCI Synthesis Model in README
2026-05-27 chore(apps): Remove Metabase and n8n due to OIDC limitations
    - Removes references to Metabase and n8n from recipes, blueprints, and config files.
    - Updates documentation to reflect the removal of services without OIDC support.
    - Adds missing .gitignore for build contexts.
2026-06-05 feat(koral): generalize genesis configuration fields
    Renamed hardwareWallet to walletType, primaryLedger to ledgerType, adminLedgerKey to adminAddress, and siweOidcRelay to oidcRelay for clarity and consistency across project constitutions.
2026-06-05 feat(koral): add BPMN modeling for human-in-the-loop workflows
    Included hasProcess references in organizational JSON-LD ontologies and created basic BPMN workflow templates for NEF stabilization review and Desertmonitor retail fulfillment.
2026-06-05 refactor(koral): migrate addons to dynamic plugin architecture
    Extracted hardcoded addon build steps from synthesis script into dedicated plugin_hook.sh files under software/koral/addons/. Repackaged the embedded mapper into the new plugin system with flexible b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
2026-06-05 docs(architecture): clarify OCI surgery and Intel SGXv2 fallback
    Specified that Koral Image generation is the result of OCI surgery and added explicit warnings/fallback behavior for Intel SGXv2 execution environments without full TDX enclaves.
2026-06-05 docs(concepts): update token utility, regional DAO merit, and liquidity depth routing dynamics
    Added concepts covering Eurovision-Style Federated Voting for global token distribution, localized Regional DAO Merit Tokens, and Liquidity Depth Reporting for probability-based routing.
2026-06-05 test(manifesto): mock podman trace generation to prevent hangs
    Replaced live podman execution in test_podman_trace with a mocked trace session creation to ensure reliable testing without hanging processes.
2026-06-05 feat(build): enhance Makefile with entity flag and add base container recipes
    Updated the build factory Makefile to support dynamic entity targets via the ENTITY flag. Added base Containerfiles for koral builds and specific authentik images.
2026-06-05 chore(koral): add entity subdirectories for governance, contracts, and treasury
    Committed remaining structural directories and files across koral entities to establish proper layout for sociological-intents, addons, contracts, and treasury.
2026-06-17 Koral not proprietary any more
